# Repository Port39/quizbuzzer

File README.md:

# Simple quiz buzzer

Features:
- Four/six inputs for buttons.
- Five/eight open collector outputs to trigger external periphery.
- 7 segment
- Powered by an ATmegaXY8(P) (e.g., an Atmega328, or even an ATmega48)

## Building and flashing the firmware

You need AVR-GCC or something compatible to build this.
Just run `make` and then `make flash`.
The latter comand uses *avrdude* to flash your µC.
You _should_ be able to build the firmware with ~~Atmel~~ Microchip Studio as well.
Set the variables of the makefile accordingly:

- `MCU` (`atmega328p`): Set to your variant of the uC (e.g., if you have an ATmega168, set it to `atmega168`)
- `F_CPU` (`1000000`): The CPU speed your controller runs at. This does not set the actual CPU speed (set fuses for that!), but just tells the compiler. Currently only `1000000` and `16000000` are supported yet.
- `PORT` (`/dev/ttyUSB0`): The port your programmer is connected to.
- `PROGRAMMER` (`arduino`): The programmer you use (see below for some common configurations)
- `BAUD` (`9600`): The baud rate of the programmer.

### Programmer and baud rate combinations

- "Arduino as ISP": `PROGRAMMER=stk500v1`, `BAUD=19200`
- USB bootloader from the Arduino project: `PROGRAMMER=arduino`, `BAUD=9600`
- "mySmartUSB light" in stk500 mode: `PROGRAMMER=stk500`, `BAUD=115200`

## Schematics

Schematics are made with KiCad.
Only standard components were used (or the used footprint is embedded).

## Revisions

The firmware is not compatible between board revisions.

### Revision 1

Revision 1 is for building on a 7x9cm prototyping board.

Depending on the pinout of your 7-segment display, you may need to change the array in *7segment.c*.

### Revision 2

Revision 2 (planned) is for soldering an manufactured PCB.
The serial (UART) outputs are available for programming (if a bootloader is flashed),
and output the current game state.

The second revision has the following upgrades:
- A CH340 on the board. This allows serial communication and programming over USB!
- Thanks to multiplexers, up to six players can play now!
- And an additional open collector "buzzer" pin is added. This allows for external buzzers circuits.
- There now is a power on LED.

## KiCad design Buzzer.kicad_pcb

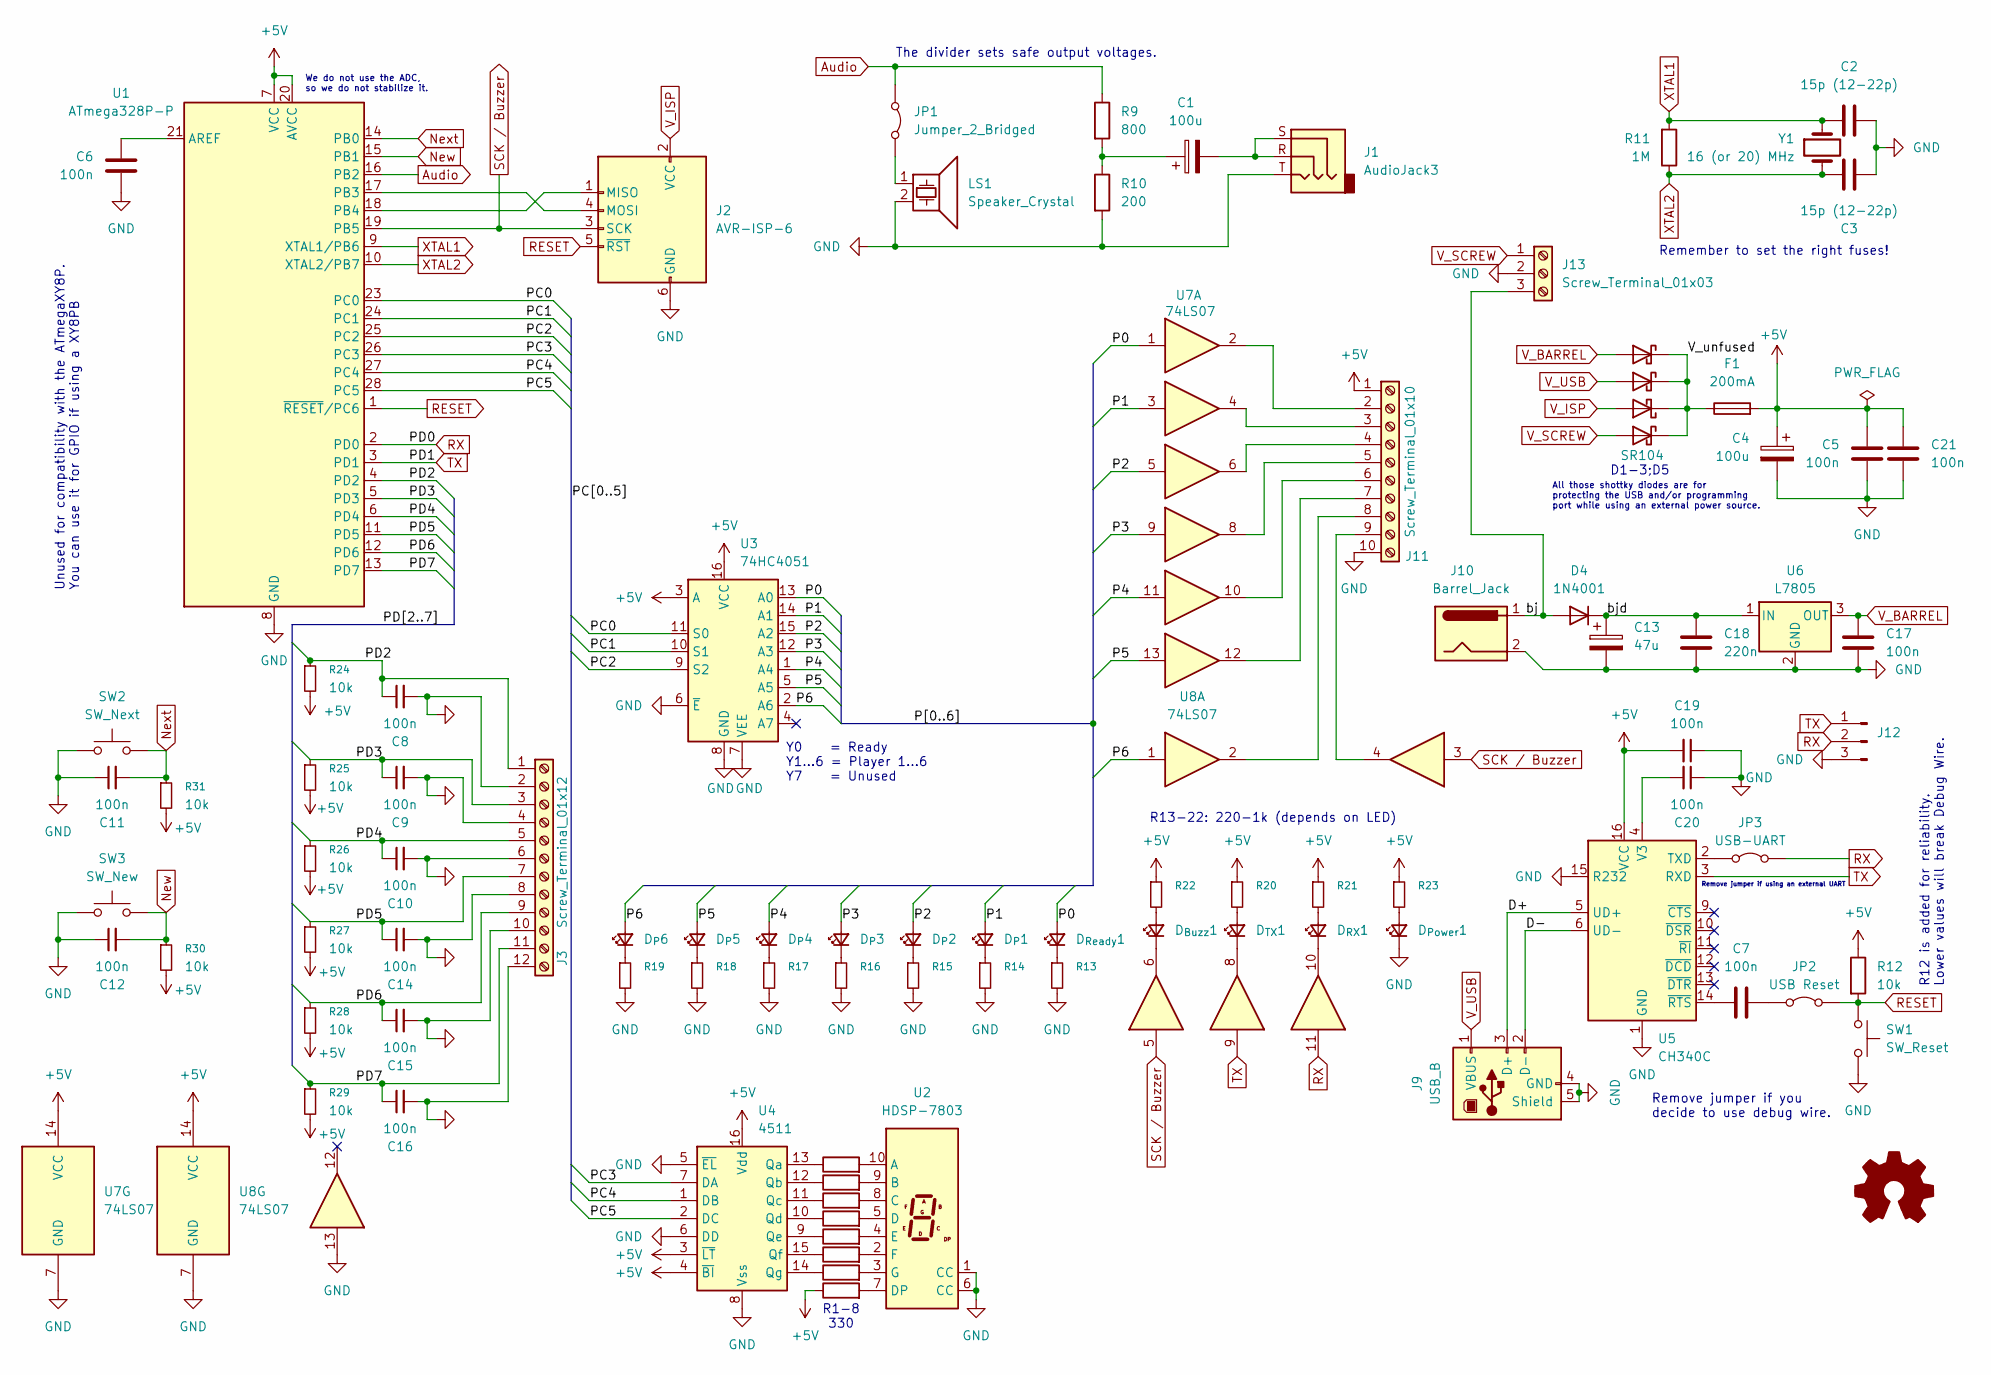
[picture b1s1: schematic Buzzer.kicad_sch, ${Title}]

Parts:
C1, C4: 100u; CP_Radial_D6.3mm_P2.50mm
C2, C3: 15p (12-22p); C_Disc_D5.0mm_W2.5mm_P5.00mm
C5, C6, C7, C8, C9, C10, C11, C12, C14, C15, C16, C17, C19, C20, C21: 100n; C_Disc_D5.0mm_W2.5mm_P2.50mm
C13: 47u; CP_Radial_D8.0mm_P3.50mm
C18: 220n; C_Disc_D5.0mm_W2.5mm_P2.50mm
D1, D2, D5: SR104; D_DO-41_SOD81_P7.62mm_Horizontal
D3: SR104; D_DO-41_SOD81_P12.70mm_Horizontal
D4: 1N4001; D_DO-41_SOD81_P7.62mm_Horizontal
D_{Buzz}1: LED_Small; LED_Rectangular_W5.0mm_H2.0mm
D_{Power}1: LED_Small; LED_Rectangular_W5.0mm_H2.0mm
D_{P}1, D_{P}2, D_{P}3, D_{P}4, D_{P}5, D_{P}6: LED_Small; LED_Rectangular_W5.0mm_H2.0mm
D_{RX}1: LED_Small; LED_Rectangular_W5.0mm_H2.0mm
D_{Ready}1: LED_Small; LED_Rectangular_W5.0mm_H2.0mm
D_{TX}1: LED_Small; LED_Rectangular_W5.0mm_H2.0mm
F1: 200mA; Fuseholder_Littelfuse_100_series_5x20mm
J1: AudioJack3; Jack_3.5mm_Ledino_KB3SPRS_Horizontal
J2: AVR-ISP-6; IDC-Header_2x03_P2.54mm_Vertical
J3: Screw_Terminal_01x12; TerminalBlock_Phoenix_MKDS-1,5-12-5.08_1x12_P5.08mm_Horizon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
J9: USB_B; USB_B_OST_USB-B1HSxx_Horizontal
J10: Barrel_Jack; BarrelJack_Kycon_KLDX-0202-xC_Horizontal
J11: Screw_Terminal_01x10; TerminalBlock_Phoenix_MKDS-1,5-10-5.08_1x10_P5.08mm_Horizon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
J12: Conn_01x03_Pin; PinHeader_1x03_P2.54mm_Vertical
J13: Screw_Terminal_01x03; TerminalBlock_Phoenix_MKDS-1,5-3-5.08_1x03_P5.08mm_Horizont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
JP1: Jumper_2_Bridged; PinHeader_1x03_P2.54mm_Vertical
JP2: USB Reset; PinHeader_1x03_P2.54mm_Vertical
JP3: USB-UART; PinHeader_1x03_P2.54mm_Vertical
LS1: Speaker_Crystal; PinHeader_1x02_P2.54mm_Vertical
R1, R2, R3, R4, R5, R6, R7, R8: 330; R_Axial_DIN0207_L6.3mm_D2.5mm_P10.16mm_Horizontal
R9: 800; R_Axial_DIN0207_L6.3mm_D2.5mm_P10.16mm_Horizontal
R10: 200; R_Axial_DIN0207_L6.3mm_D2.5mm_P10.16mm_Horizontal
R11: 1M; R_Axial_DIN0207_L6.3mm_D2.5mm_P10.16mm_Horizontal
R12, R25, R28, R30, R31: 10k; R_Axial_DIN0207_L6.3mm_D2.5mm_P10.16mm_Horizontal
R13, R14, R15, R16, R17, R18, R19, R20, R21, R22, R23: 220-1k; R_Axial_DIN0207_L6.3mm_D2.5mm_P10.16mm_Horizontal
R24, R29: 10k; R_Axial_DIN0207_L6.3mm_D2.5mm_P7.62mm_Horizontal
R26, R27: 10k; R_Axial_DIN0207_L6.3mm_D2.5mm_P15.24mm_Horizontal
SW1: SW_Reset; SW_PUSH_6mm
SW2: SW_Next; SW_PUSH_6mm
SW3: SW_New; SW_PUSH_6mm
U1: ATmega328P-P; DIP-28_W7.62mm_Socket
U2: HDSP-7803; HDSP-7801
U3: 74HC4051; DIP-16_W7.62mm_Socket
U4: 4511; DIP-16_W7.62mm_Socket
U5: CH340C; SOIC-16_3.9x9.9mm_P1.27mm
U6: L7805; TO-220-3_Horizontal_TabDown
U7, U8: 74LS07; DIP-14_W7.62mm_Socket
Y1: 16 (or 20) MHz; Crystal_HC49-U_Vertical

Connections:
+5V: C4.1, C5.2, C19.2, C21.2, F1.2, J11.1, R8.1, R12.1, R20.1, R21.1, R22.1, R23.1, R24.2, R25.2, R26.2, R27.2, R28.2, R29.2, R30.2, R31.2, U1.7 (VCC), U1.20 (AVCC), U3.3 (A), U3.16 (VCC), U4.3 (~LT), U4.4 (~BI), U4.16 (Vdd), U5.16 (VCC), U7.14 (VCC), U8.14 (VCC)
/D+: J9.3 (D+), U5.5 (UD+)
/D-: J9.2 (D-), U5.6 (UD-)
/P0: D_{Ready}1.2 (A), U3.13 (A0), U7.1
/P1: D_{P}1.2 (A), U3.14 (A1), U7.3
/P2: D_{P}2.2 (A), U3.15 (A2), U7.5
/P3: D_{P}3.2 (A), U3.12 (A3), U7.9
/P4: D_{P}4.2 (A), U3.1 (A4), U7.11
/P5: D_{P}5.2 (A), U3.5 (A5), U7.13
/P6: D_{P}6.2 (A), U3.2 (A6), U8.1
/PC0: U1.23 (PC0), U3.11 (S0)
/PC1: U1.24 (PC1), U3.10 (S1)
/PC2: U1.25 (PC2), U3.9 (S2)
/PC3: U1.26 (PC3), U4.7 (DA)
/PC4: U1.27 (PC4), U4.1 (DB)
/PC5: U1.28 (PC5), U4.2 (DC)
/PD2: C8.1, J3.1, R24.1, U1.4 (PD2)
/PD3: C9.1, J3.3, R25.1, U1.5 (PD3)
/PD4: C10.1, J3.5, R26.1, U1.6 (PD4)
/PD5: C14.1, J3.7, R27.1, U1.11 (PD5)
/PD6: C15.1, J3.9, R28.1, U1.12 (PD6)
/PD7: C16.1, J3.11, R29.1, U1.13 (PD7)
/V_unfused: D1.1 (K), D2.1 (K), D3.1 (K), D5.1 (K), F1.1
/bj: D4.2 (A), J10.1, J13.3
/bjd: C13.1, C18.1, D4.1 (K), U6.1 (IN)
Audio: JP1.1 (A), R9.1, U1.16 (PB2)
GND: C2.2, C3.2, C4.2, C5.1, C6.1, C8.2, C9.2, C10.2, C11.1, C12.1, C13.2, C14.2, C15.2, C16.2, C17.2, C18.2, C19.1, C20.1, C21.1, D_{Power}1.1 (K), J1.T, J2.6 (GND), J3.2, J3.4, J3.6, J3.8, J3.10, J3.12, J9.4 (GND), J9.5 (Shield), J10.2, J11.10, J12.3, J13.2, LS1.2, R10.2, R13.2, R14.2, R15.2, R16.2, R17.2, R18.2, R19.2, SW1.2, SW2.1, SW3.1, U1.8 (GND), U1.22 (GND), U2.1 (CC), U2.6 (CC), U3.6 (~E), U3.7 (VEE), U3.8 (GND), U4.5 (~EL), U4.6 (DD), U4.8 (Vss), U5.1 (GND), U5.15 (R232), U6.2 (GND), U7.7 (GND), U8.7 (GND), U8.13
unnamed: C1.1, R9.2, R10.1
unnamed: C1.2, J1.R, J1.S
unnamed: D_{Buzz}1.2 (A), R22.2
unnamed: D_{Buzz}1.1 (K), U8.6
unnamed: D_{Power}1.2 (A), R23.2
unnamed: D_{P}1.1 (K), R14.1
unnamed: D_{P}2.1 (K), R15.1
unnamed: D_{P}3.1 (K), R16.1
unnamed: D_{P}4.1 (K), R17.1
unnamed: D_{P}5.1 (K), R18.1
unnamed: D_{P}6.1 (K), R19.1
unnamed: D_{RX}1.2 (A), R21.2
unnamed: D_{RX}1.1 (K), U8.10
unnamed: D_{Ready}1.1 (K), R13.1
unnamed: D_{TX}1.2 (A), R20.2
unnamed: D_{TX}1.1 (K), U8.8
unnamed: J2.1 (MISO), U1.18 (PB4)
unnamed: J2.4 (MOSI), U1.17 (PB3)
unnamed: J11.2, U7.2
unnamed: J11.3, U7.4
unnamed: J11.4, U7.6
unnamed: J11.5, U7.8
unnamed: J11.6, U7.10
unnamed: J11.7, U7.12
unnamed: J11.8, U8.2
unnamed: J11.9, U8.4
unnamed: JP1.2 (B), LS1.1
unnamed: C7.2, JP2.1 (A)
unnamed: JP3.1 (A), U5.2 (TXD)
unnamed: C6.2, U1.21 (AREF)
unnamed: R1.2, U2.10 (A)
unnamed: R2.2, U2.9 (B)
unnamed: R3.2, U2.8 (C)
unnamed: R4.2, U2.5 (D)
unnamed: R8.2, U2.7 (DP)
unnamed: R5.2, U2.4 (E)
unnamed: R6.2, U2.2 (F)
unnamed: R7.2, U2.3 (G)
unnamed: R1.1, U4.13 (Qa)
unnamed: R2.1, U4.12 (Qb)
unnamed: R3.1, U4.11 (Qc)
unnamed: R4.1, U4.10 (Qd)
unnamed: R5.1, U4.9 (Qe)
unnamed: R6.1, U4.15 (Qf)
unnamed: R7.1, U4.14 (Qg)
unnamed: C20.2, U5.4 (V3)
unnamed: C7.1, U5.14 (~RTS)
New: C12.2, R30.1, SW3.2, U1.15 (PB1)
Next: C11.2, R31.1, SW2.2, U1.14 (PB0)
RESET: J2.5 (~RST), JP2.2 (B), R12.2, SW1.1, U1.1 (~RESET/PC6)
RX: J12.2, JP3.2 (B), U1.2 (PD0), U8.11
SCK / Buzzer: J2.3 (SCK), U1.19 (PB5), U8.3, U8.5
TX: J12.1, U1.3 (PD1), U5.3 (RXD), U8.9
V_BARREL: C17.1, D1.2 (A), U6.3 (OUT)
V_ISP: D3.2 (A), J2.2 (VCC)
V_SCREW: D5.2 (A), J13.1
V_USB: D2.2 (A), J9.1 (VBUS)
XTAL1: C2.1, R11.2, U1.9 (XTAL1/PB6), Y1.1
XTAL2: C3.1, R11.1, U1.10 (XTAL2/PB7), Y1.2

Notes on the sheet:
D1-3;D5
R1-8 330
We do not use the ADC, so we do not stabilize it.
Y0 = Ready Y1...6 = Player 1...6 Y7 = Unused
Remember to set the right fuses!
All those shottky diodes are for protecting the USB and/or programming port while using an external power source.
R12 is added for reliability. Lower values will break Debug Wire.
Remove jumper if you decide to use debug wire.
The divider sets safe output voltages.
R13-22: 220-1k (depends on LED)
Unused for compatibility with the ATmegaXY8P. You can use it for GPIO if using a XY8PB
Remove jumper if using an external UART

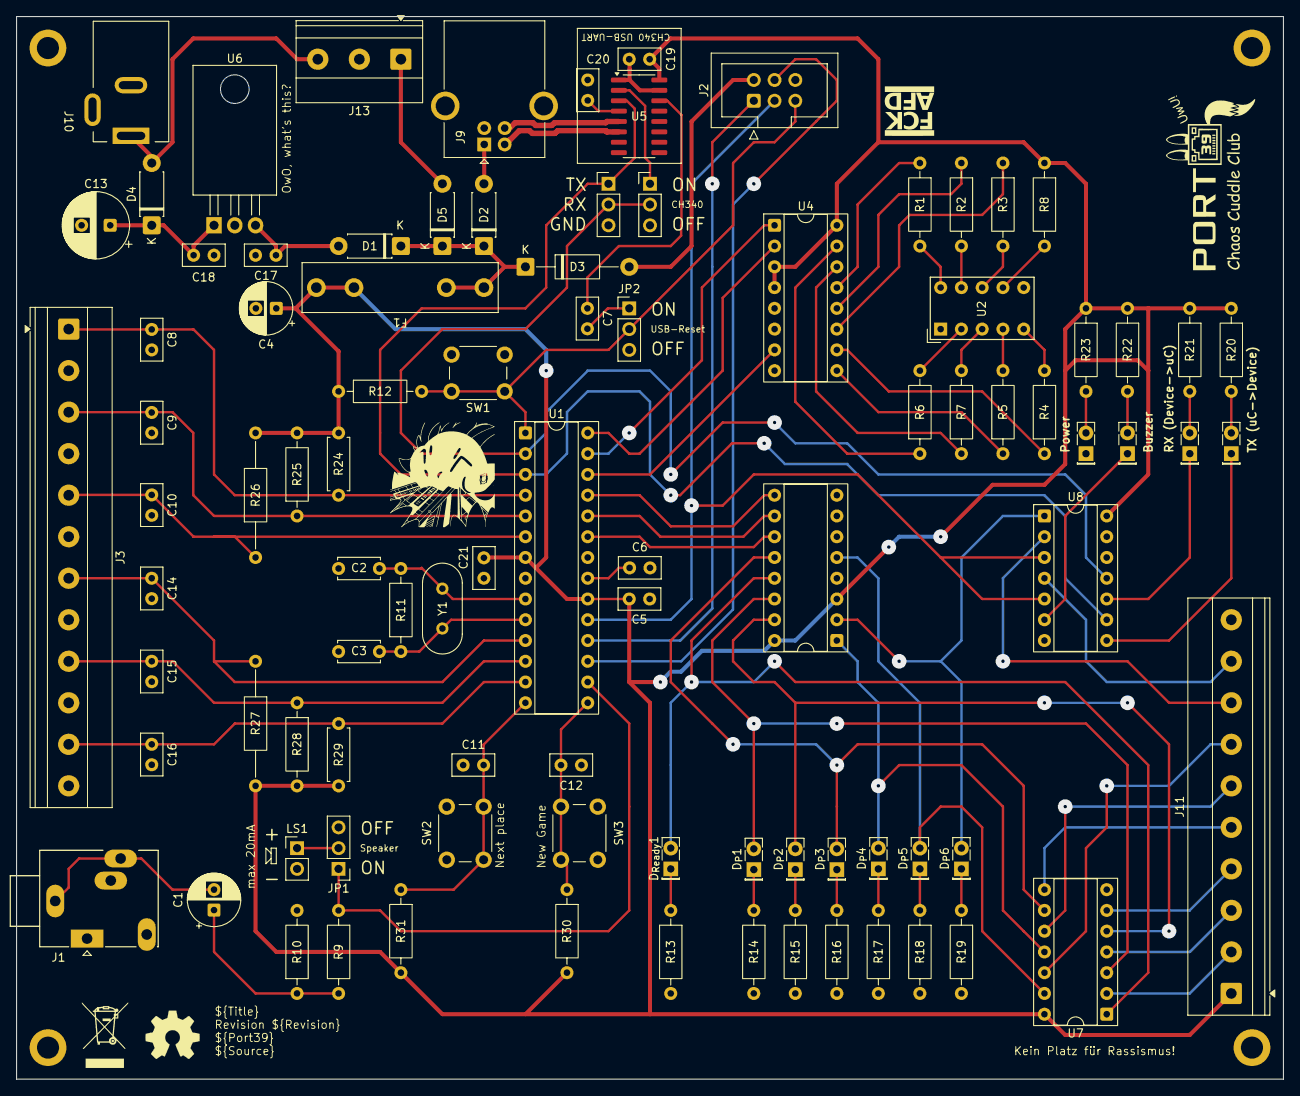
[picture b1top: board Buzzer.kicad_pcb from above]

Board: 2 copper layers, 155.0 x 130.0 mm, 93 parts (0 on the bottom side), 86 nets.

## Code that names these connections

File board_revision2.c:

// SPDX-License-Identifier: MPL-2.0
// Copyright (c) 2025 Simon Biewald
//
// Interface implementations for board revision 2.
//
// +--------+
// |    PB0 | Next
// |    PB1 | New
// |    PB2 | Buzzer (Audio)
// |    PB5 | Ext. Buzzer
// |        |
// | PC0..2 | Ready, Player 1..6 (BCD)
// | PC3..5 | 7-segment (BCD)
// |        |
// |    PD0 | RX
// |    PD1 | TX
// | PD2..7 | Player 1..6 (Input)
// +--------+

#if BOARD_REVISION == 2
#include "board.h"

#include <avr/io.h>
#include <avr/interrupt.h>
#include <util/delay.h>
#include <stdio.h>

// #include "board_revision2.h"

#include "logic.h"

void setupHardware(void) {
    // Next, New
    DDRB &= ~(1 << PIN0) | (1 << PIN1);
    // Next, New (Pull up)
    PORTB |= (1 << PIN0);
    PORTB |= (1 << PIN1);

    // Buzzer (Audio)
    DDRB |= (1 << PIN2);
    // Buzzer (external trigger)
    DDRB |= (1 << PIN5);

    // Ready and player 1-6 LEDs
    DDRC |= (1 << PIN0) | (1 << PIN1) | (1 << PIN2);
    // 7-segment
    DDRC |= (1 << PIN3) | (1 << PIN4) | (1 << PIN5);
    // Set output to 0
    PORTC &= ~(1 << PIN0) | (1 << PIN1) | (1 << PIN2) | (1 << PIN3) | (1 << PIN4) | (1 << PIN5);

    // Player 1-6 buttons
    DDRD &= ~(1 << PIN2) | (1 << PIN3) | (1 << PIN4) | (1 << PIN5) | (1 << PIN6) | (1 << PIN7);
    // Player 1-6 buttons (pull up)
    PORTD |= (1 << PIN2) | (1 << PIN3) | (1 << PIN4) | (1 << PIN5) | (1 << PIN6) | (1 << PIN7);

    // Ensure capacitors are charged before enabling interrupts;
    // it would trigger a "buzzer" event otherwise.
    // This is strictly only necessary after a full board reset which we don't track.
    _delay_ms(100);

    // Enable interrupts for PORTD
    PCICR |= (1 << PCIE2);
    // Enable interrupts on PIN PD7..2 (PCINT23..18)
    PCMSK2 |= (1 << PCINT23) | (1 << PCINT22) | (1 << PCINT21) | (1 << PCINT20) | (1 << PCINT19) | (1 << PCINT18);

    // Enable interrupts for PORTB
    PCICR |= (1 << PCIE0);
    // Players + New Game PIN PB1..0 (PCINT1..0)
    PCMSK0 |= (1 << PCINT1) | (1 << PCINT0);
}


void setDigit(int digit) {
    // We only set three bits.
    if (digit >= 7) return;
    PORTC &= ~(7 << 3);
    PORTC |= (digit << 3);
}

void highlightPlayer(unsigned char player) {
    if (player == PLAYER_PLACEHOLDER) {
        PORTC &= ~7;
    }
    if (player > MAX_PLAYERS) return;
    // Player 0 would be game ready
    PORTC = (PORTC & ~7) | player + 1;
}

void toggleBuzzer(void) {
    PORTB ^= (1 << PIN2);
}

void setBuzzerActive(bool active) {
    if (active) {
        PORTB |= (1 << PIN5);
    } else {
        PORTB &= ~(1 << PIN5);
    }
}


ISR(PCINT0_vect) {
    if (!(PINB & (1 << PIN0))) nextPlayer();
    if (!(PINB & (1 << PIN1))) newGame();
}


ISR(PCINT2_vect) {
    for (int i = PIN2; i <= PIN7; i++) {
        // If the button is "up" (pull-up connects it with +5V), check next.
        if (PIND & (1 << i)) continue;
        addPlayer(i - PIN2);
        buzz(1000);
    }
}

#endif

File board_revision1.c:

// SPDX-License-Identifier: MPL-2.0
// Copyright (c) 2025 Simon Biewald
//
// Interface implementations for board revision 1.
//
// +--------+
// |    PB0 | Next
// |    PB1 | Buzzer (Audio)
// | PB2..5 | Player 1..4
// |        |
// |    PC0 | Ready
// |  PC1-4 | Player 1..4 (Input)
// |    PC5 | New
// |        |
// | PD0..7 | 7-segment (potentially cursed pinout)
// +--------+

#if BOARD_REVISION == 1
#include <avr/io.h>
#include <avr/interrupt.h>
#include <util/delay.h>

#include "board.h"
#include "board_revision1.h"

#include "logic.h"

void setupHardware(void) {
    // Buzzer
    DDRB |= (1 << PIN1);

    // "Player 1-4 is active" LEDs
    DDRB |= (1 << PIN2);
    DDRB |= (1 << PIN3);
    DDRB |= (1 << PIN4);
    DDRB |= (1 << PIN5);

    // Enable pull-up for the "next player" button.
    PORTB |= (1 << PIN0);

    DDRC |=  (1 << PIN0);  // green LED
    DDRC &= ~(1 << PIN1);  // P1
    DDRC &= ~(1 << PIN2);  // P2
    DDRC &= ~(1 << PIN3);  // P3
    DDRC &= ~(1 << PIN4);  // P4
    DDRC &= ~(1 << PIN5);  // New Game

    // Enable pull-up resistors for P1-4
    // Buttons connect the pin with +5V
    PORTC |= (1 << PIN1);
    PORTC |= (1 << PIN2);
    PORTC |= (1 << PIN3);
    PORTC |= (1 << PIN4);
    PORTC |= (1 << PIN5);

    // 7-segment output
    DDRD = 0xff;

    // Ensure capacitors are charged before enabling interrupts.
    _delay_ms(100);

    // Enable interrupts for PCINT8-14 (though we only use 9-13; PORTC1-5)
    PCICR |= (1 << PCIE1);
    // Players + New Game
    PCMSK1 |= (1 << PCINT9) | (1 << PCINT10) | (1 << PCINT11) | (1 << PCINT12) | (1 << PCINT13);
    // Next player
    PCICR |= (1 << PCIE0);
    PCMSK0 |= (1 << PCINT0);
}


static uint8_t chars [16] = {
        SEGMENT_A | SEGMENT_B | SEGMENT_C | SEGMENT_D | SEGMENT_E | SEGMENT_F,
        SEGMENT_B | SEGMENT_C,
        SEGMENT_A | SEGMENT_B | SEGMENT_G | SEGMENT_E | SEGMENT_D,
        SEGMENT_A | SEGMENT_B | SEGMENT_G | SEGMENT_C | SEGMENT_D,
        SEGMENT_F | SEGMENT_G | SEGMENT_B | SEGMENT_C,
        SEGMENT_A | SEGMENT_F | SEGMENT_G | SEGMENT_C | SEGMENT_D,
        SEGMENT_A | SEGMENT_B | SEGMENT_G | SEGMENT_E | SEGMENT_D | SEGMENT_C,
        SEGMENT_A | SEGMENT_B | SEGMENT_C,
        SEGMENT_A | SEGMENT_B | SEGMENT_C | SEGMENT_D | SEGMENT_E | SEGMENT_F | SEGMENT_G,
        SEGMENT_A | SEGMENT_B | SEGMENT_C | SEGMENT_D | SEGMENT_F | SEGMENT_G,
};


void setDigit(int digit) {
    if (digit >= 16) return;
#ifdef INVERT_SEGMENTS
    PORTD = 0xff & (~chars[digit]);
#else
    PORTD = chars[value];
#endif
}

void highlightPlayer(unsigned char player) {
    if (player > MAX_PLAYERS && player != PLAYER_PLACEHOLDER) return;
    PORTB &= 0xc3;
    if (player == PLAYER_PLACEHOLDER) {
        PORTC |= 1 << PIN0;
        return;
    }
    PORTB |= (1 << (player + PIN2));
    PORTC &= ~(1 << PIN0);
}

void toggleBuzzer(void) {
    PORTB ^= (1 << PIN1);
}

void setBuzzerActive(bool active) {
    // no-op
    (void)active;
}


ISR(PCINT1_vect) {
        // Check if pins are triggered
        for (int i = 0; i < 5; i++) {
            if ((PINC & (1 << (PIN1 + i)))) continue;

            if (i<4) {
                // Player button
                addPlayer(i);
                buzz(1000);
            } else {
                newGame();
            }
        }
}

ISR(PCINT0_vect) {
    // Skip the "up" event.
    if (PINB & (1 << PIN0)) return;

    nextPlayer();
}

#endif

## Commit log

2025-06-25 Initial commit.
2025-07-17 Remove code generator.
2025-07-21 Add hint for 'true' STK500 programmer.
2025-07-22 Add revision 2 circuit, pcb and documentation.
2025-07-22 Add license files.
2025-07-22 Add gerber files.
2025-07-22 Config changes.
2025-08-06 Set schematic revisions by variables.
2025-08-06 Restructure code to be compatible with both board revisions.

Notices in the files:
parts and their libraries:
License: CERN-OHL-W
